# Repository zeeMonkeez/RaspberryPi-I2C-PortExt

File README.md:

RaspberryPi-I2C-PortExt
=======================

This is a 5V I2C 8bit port extender for RaspberryPi using an MCP23008.
Use this to connect up to 8 digital lines as inputs or outputs, with a programmable interrupt line to notify RaspberryPi of changes.
All at the 5V level.

Using an appropriate header/socket (e.g. SAMTEC ESQ-113-24-T-D, Farnell 1930727) the module is stackable.
Pinheader X3 can be fitted to select the address of the MCP with jumpers. If not fitted, wire jumpers have to be soldered in.
X4 can be soldered in so the /RST and INT lines can be connected to GPIO lines.
The I2C lines and /RST are protected by MOSFETs (according to NXP's application note). INT is level shifted using a 74LVC1G07DCK buffer. The buffer's output again is protected through R6 against accidentally setting the GPIO it's connected to as an output.
If /RST is not needed, T3 and R4 do not have to be fitted. If INT is not needed, IC2 and R6 can be left out.
For C1/C4 and C2/C3, SMD or through hole components can be used.

License
-------
<br />This work is licensed under a <a rel="license" href="http://creativecommons.org/licenses/by-sa/2.0/uk/">Creative Commons Attribution-ShareAlike 2.0 UK: England &amp; Wales License</a>.

&copy;2012 Jonas Zimmermann.

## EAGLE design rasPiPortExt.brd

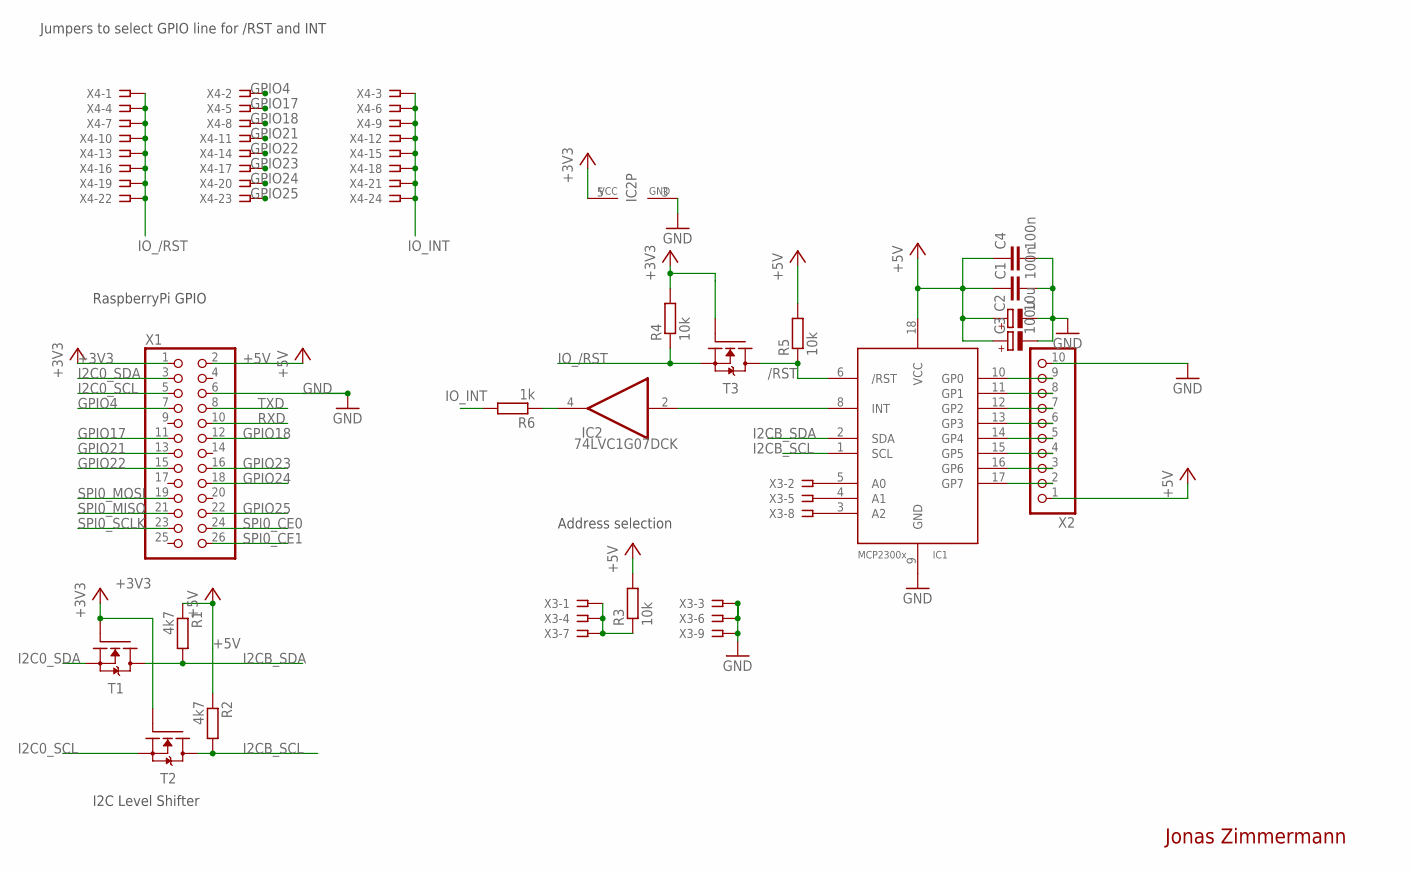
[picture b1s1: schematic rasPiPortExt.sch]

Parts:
C1: 100n; C1206
C2: 10u; PANASONIC_C
C3: 100u; E2,5-5
C4: 100n; C050-025X075
IC1: MCP2300X/P; DIL18
IC2: 74LVC1G07DCK; SC70-5
R1, R2: 4k7; R0805
R3, R4, R5: 10k; R0805
R6: 1k; R0805
T1, T2, T3: BSS138PW"; SOT-323
X1: PINHD-2X13; 2X13
X2: PINHD-1X10; 1X10
X3: SSW-103-02-S-T
X4: SSW-108-02-S-T

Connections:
+3V3: IC2.5 (VCC), R4.2, T1.P$1 (G), T2.P$1 (G), T3.P$1 (G), X1.1
+5V: C1.1, C2.+, C3.+, C4.1, IC1.18 (VCC), R1.1, R2.1, R3.2, R5.2, X1.2, X2.1
/RST: IC1.6 (/RST), R5.1, T3.P$3 (D)
GND: C1.2, C2.-, C3.-, C4.2, IC1.9 (GND), IC2.3 (GND), X1.6, X2.10, X3.3, X3.6, X3.9
GPIO4: X1.7, X4.2
GPIO17: X1.11, X4.5
GPIO18: X1.12, X4.8
GPIO21: X1.13, X4.11
GPIO22: X1.15, X4.14
GPIO23: X1.16, X4.17
GPIO24: X1.18, X4.20
GPIO25: X1.22, X4.23
I2C0_SCL: T2.P$2 (S), X1.5
I2C0_SDA: T1.P$2 (S), X1.3
I2CB_SCL: IC1.1 (SCL), R2.2, T2.P$3 (D)
I2CB_SDA: IC1.2 (SDA), R1.2, T1.P$3 (D)
INT: IC1.8 (INT), IC2.2 (I)
IO_/RST: R4.1, T3.P$2 (S), X4.1, X4.4, X4.7, X4.10, X4.13, X4.16, X4.19, X4.22
IO_INT: R6.2, X4.3, X4.6, X4.9, X4.12, X4.15, X4.18, X4.21, X4.24
unnamed: IC1.5 (A0), X3.2
unnamed: IC1.4 (A1), X3.5
unnamed: IC1.3 (A2), X3.8
unnamed: IC1.10 (GP0), X2.9
unnamed: IC1.11 (GP1), X2.8
unnamed: IC1.12 (GP2), X2.7
unnamed: IC1.13 (GP3), X2.6
unnamed: R3.1, X3.1, X3.4, X3.7
unnamed: IC1.14 (GP4), X2.5
unnamed: IC1.15 (GP5), X2.4
unnamed: IC1.16 (GP6), X2.3
unnamed: IC1.17 (GP7), X2.2
unnamed: IC2.4 (O), R6.1
RXD: X1.10
SPI0_CE0: X1.24
SPI0_CE1: X1.26
SPI0_MISO: X1.21
SPI0_MOSI: X1.19
SPI0_SCLK: X1.23
TXD: X1.8

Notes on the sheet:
Jumpers to select GPIO line for /RST and INT
Address selection
RaspberryPi GPIO
I2C Level Shifter
Jonas Zimmermann

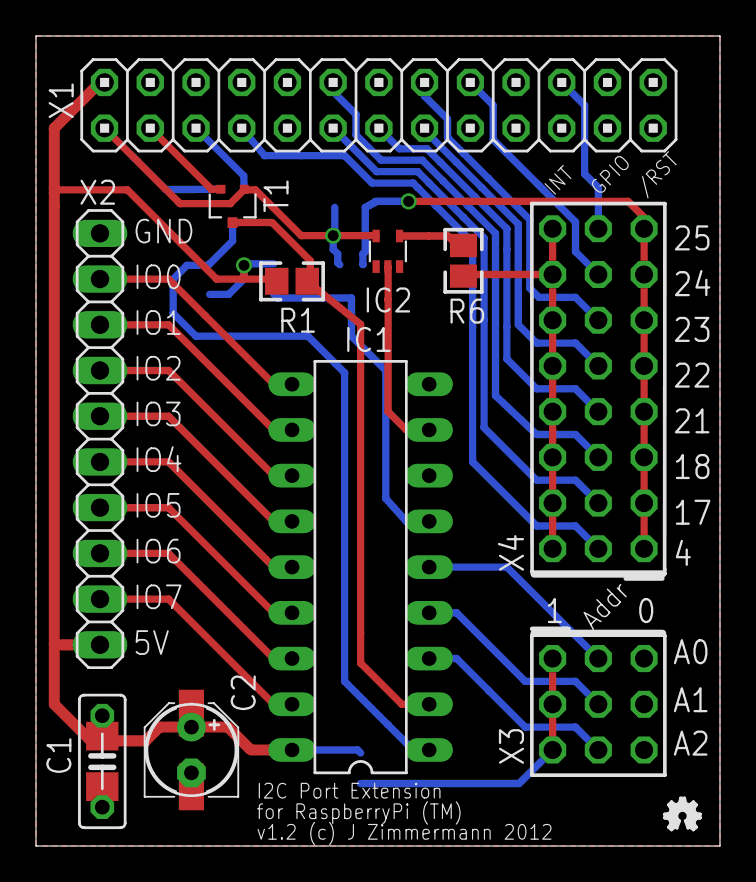
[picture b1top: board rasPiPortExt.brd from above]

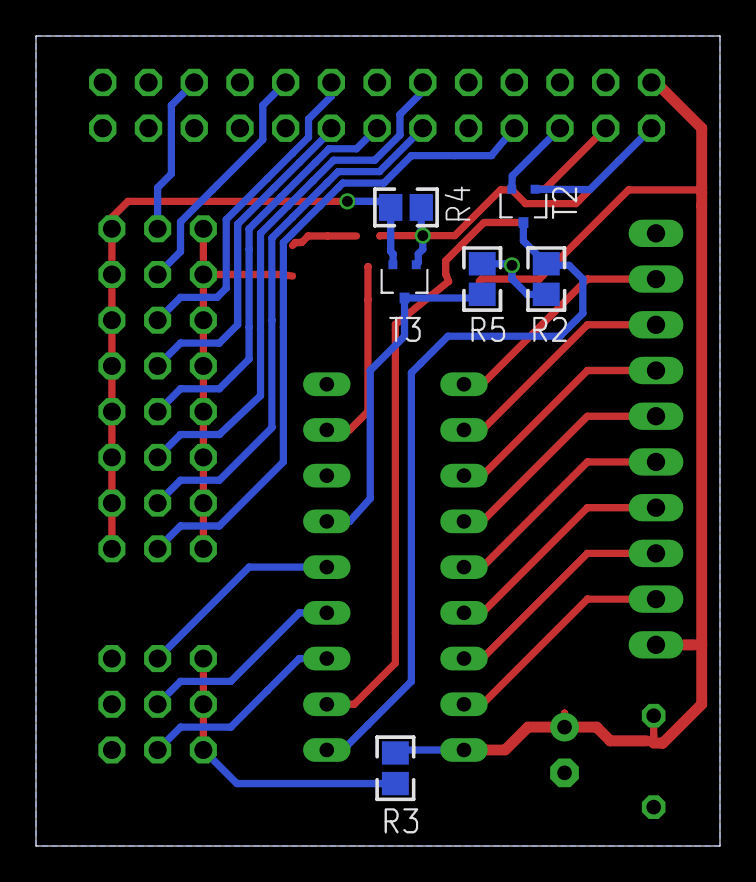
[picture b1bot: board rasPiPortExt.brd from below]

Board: 2 copper layers, 38.0 x 45.0 mm, 20 parts (6 on the bottom side), 32 nets.

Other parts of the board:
U$1: OSHW_FILLX70_NOTEXT

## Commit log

2012-06-24 folder structure
2012-06-24 version 1
2012-06-24 tagged prototype 1.0
2012-06-24 changed design for /RST line, added additional R rearranged some components and traces v1.1 submitted for etching
2012-06-24 tagged v 1.1
2012-06-25 improved buffer for IRQ line, adding protection resistor
2012-06-25 added open source hardware logo
2012-06-26 Moved a few components around, added README
2012-06-26 Added PNGs for board and schematics
2012-06-26 Added comment 5V level
